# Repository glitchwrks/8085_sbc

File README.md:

# Glitch Works 8085 SBC

This repository contains the recovered EAGLE projects for the various PC boards designed as part of the Glitch Works 8085 SBC projects. These designs have been manufactured and tested and generally found to be functional; however, no warranty is made as to their fitness for any purpose. Please see the [LICENSE](https://github.com/glitchwrks/8085_sbc/blob/master/LICENSE) file for more information.

If you are interested in obtaining a bare circuit board, kit, or assembled board, please contact us through GitHub or [the Glitch Works contact form](https://services.theglitchworks.net/ng/messages/new). There's a chance we'll already have a bare board on hand, since later boards were ordered through [OSH Park](https://oshpark.com/) and resulted in three boards.

If you decide to produce any of these designs, or assemble a board from the provided schematics, please let us know through GitHub or [the Glitch Works contact form](https://services.theglitchworks.net/ng/messages/new).

### 8085 SBC rev 1

This is the original PC board produced from the "mess of wires" that started my exploration into the 8085 CPU! You can read more about the board's evolution and design [here](http://users.glitchwrks.com/~glitch/2010/09/02/8085-sbc). This board was meant to be the CPU board in a stack of boards, and contains 8K EPROM, 8K static RAM, an 8085, and associated clock generation and memory decode circuitry. You can flash a LED on the SOD pin with nothing more than this basic hardware.

### 8085 SBC rev 2

An extension of the rev 1 design, this board incorporates more RAM and ROM, mounting holes, and a few other features. Read about the board [here](http://users.glitchwrks.com/~glitch/2011/10/29/sbc-rev-2).

[AN0001 describes ROM jumpers](https://github.com/glitchwrks/8085_sbc/blob/master/8085_sbc_rev2/an0001_jumpers.txt) for socket IC3.

### I/O Board

This board contains a Zilog SCC (two channel USART) and Intel 8255 PPI to provide two serial ports and 24 bits of parallel I/O. It stacks on top of the 8085 SBC board, PC-104 style. Read about design and testing [here](http://users.glitchwrks.com/~glitch/2017/04/24/8085-io-board). I wrote a [ROM monitor](https://github.com/glitchwrks/gwmon-80) that works with this board. This was on display at [HOPE Number Nine](http://hope.net/) with the vintage computer guys.

There's an [ECO for old etches](https://github.com/glitchwrks/8085_sbc/blob/master/io_board/eco0007.txt) that is relevant if you got one of these boards from us before 2023. It corrects a routing error w.r.t. the 8255 PPI reset signal. See the linked writeup above for a picture documenting the fix.

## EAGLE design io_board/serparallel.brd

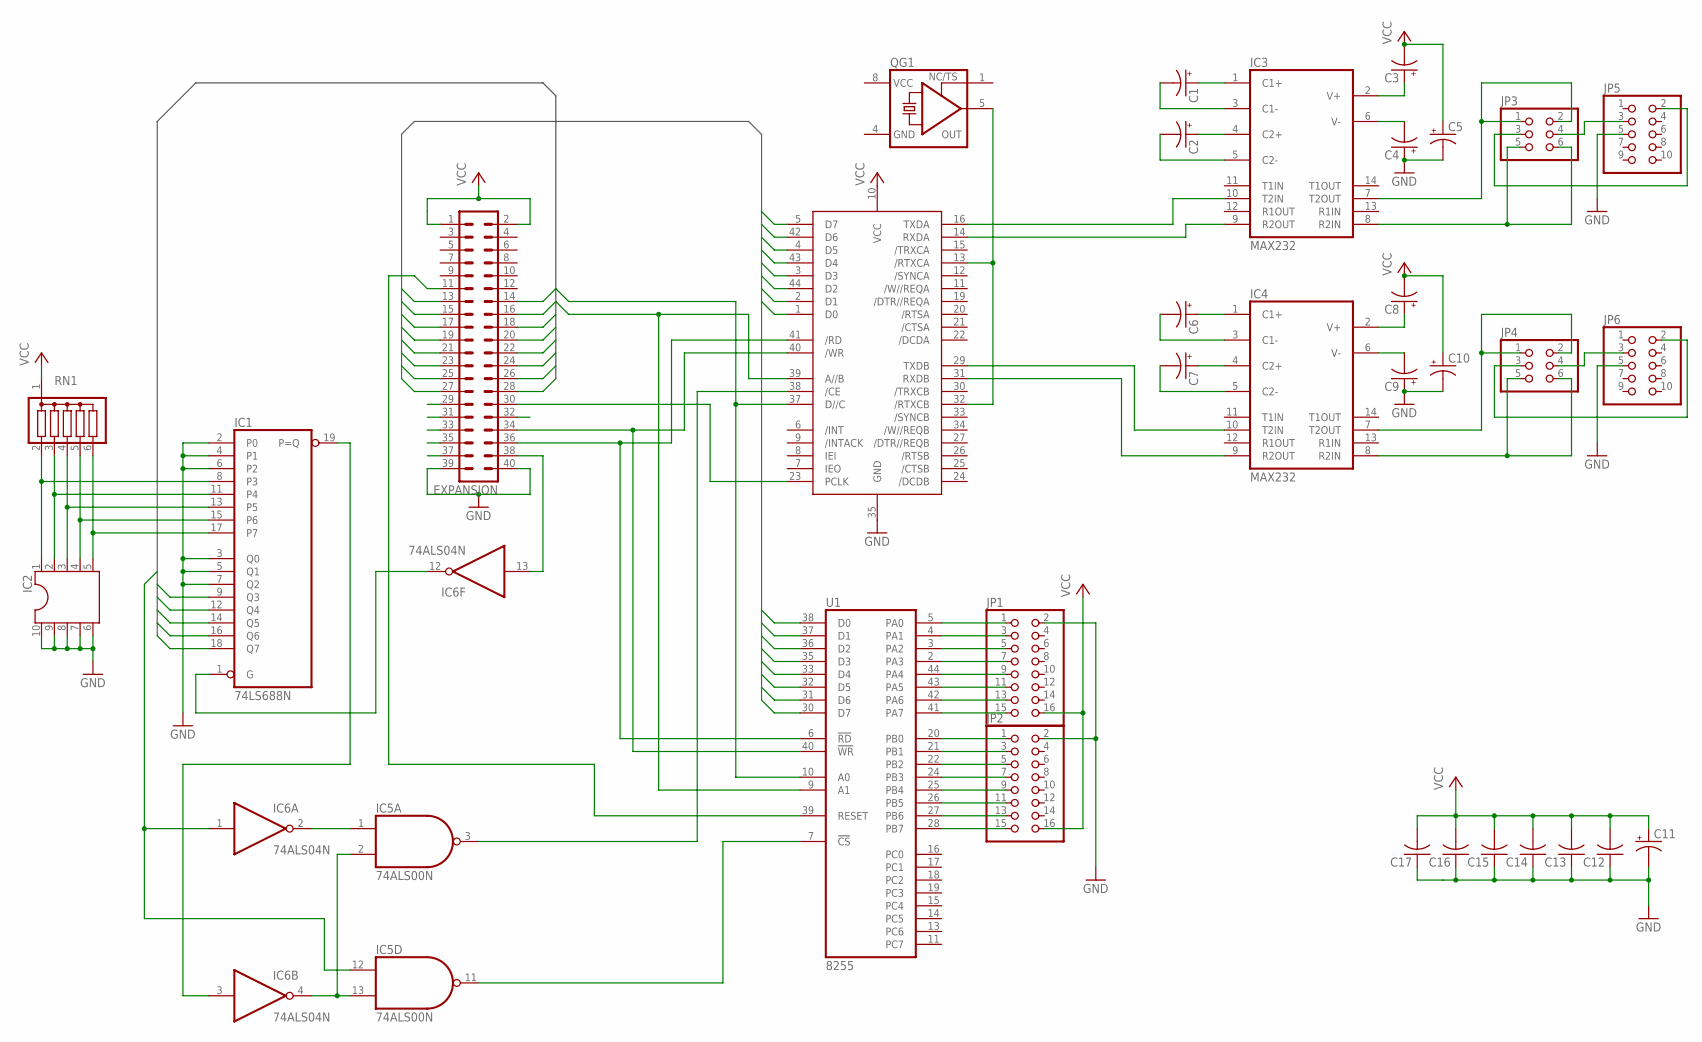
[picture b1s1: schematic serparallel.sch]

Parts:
C1, C2, C3, C4, C5, C6, C7, C8, C9, C10: CPOL-USE2,5-6E; E2,5-6E
C11: CPOL-USE15-6AXIAL; E15-6
C12, C13, C14, C15, C16, C17: C-US075-032X103; C075-032X103
EXPANSION: MA20-2W
IC1: 74LS688N; DIL20
IC2: DIL10
IC3, IC4: MAX232; DIL16
IC5: 74ALS00N; DIL14
IC6: 74ALS04N; DIL14
JP1, JP2: PINHD-2X8/90; 2X08/90
JP3, JP4: PINHD-2X3; 2X03
JP5, JP6: PINHD-2X5/90; 2X05/90
QG1: XO-8; DIL08S
RN1: G05R; SIL6
U1: 8255; S44
U2: Z8530; S44

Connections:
/RD: EXPANSION.36, U1.6 (!RD), U2.41 (/RD)
/WR: EXPANSION.34, U1.40 (!WR), U2.40 (/WR)
ADDRESS8: EXPANSION.14, U1.10 (A0), U2.37 (D//C)
ADDRESS9: EXPANSION.16, U1.9 (A1), U2.39 (A//B)
ADDRESS10: EXPANSION.18, IC5.12 (I0), IC6.1 (I)
ADDRESS11: EXPANSION.20, IC1.9 (Q3)
ADDRESS12: EXPANSION.22, IC1.12 (Q4)
ADDRESS13: EXPANSION.24, IC1.14 (Q5)
ADDRESS14: EXPANSION.26, IC1.16 (Q6)
ADDRESS15: EXPANSION.28, IC1.18 (Q7)
ALE: EXPANSION.32
CLKOUT: EXPANSION.30, U2.23 (PCLK)
DATA0: EXPANSION.27, U1.38 (D0), U2.1 (D0)
DATA1: EXPANSION.25, U1.37 (D1), U2.2 (D1)
DATA2: EXPANSION.23, U1.36 (D2), U2.44 (D2)
DATA3: EXPANSION.21, U1.35 (D3), U2.3 (D3)
DATA4: EXPANSION.19, U1.33 (D4), U2.43 (D4)
DATA5: EXPANSION.17, U1.32 (D5), U2.4 (D5)
DATA6: EXPANSION.15, U1.31 (D6), U2.42 (D6)
DATA7: EXPANSION.13, U1.30 (D7), U2.5 (D7)
GND: C4.+, C5.-, C9.+, C10.-, C11.-, C12.1, C13.1, C14.1, C15.1, C16.1, C17.1, EXPANSION.39, EXPANSION.40, IC1.2 (P0), IC1.3 (Q0), IC1.4 (P1), IC1.5 (Q1), IC1.6 (P2), IC1.7 (Q2), IC1.10 (GND), IC2.6, IC2.7, IC2.8, IC2.9, IC2.10, IC3.15 (GND), IC4.15 (GND), IC5.7 (GND), IC6.7 (GND), JP1.2, JP2.2, JP5.5, JP6.5, QG1.4 (GND), U1.8 (GND), U2.35 (GND)
INTBUS0: EXPANSION.37
INTBUS1: EXPANSION.35
INTBUS2: EXPANSION.33
INTBUS3: EXPANSION.31
INTBUS4: EXPANSION.29
IO/M: EXPANSION.38, IC6.13 (I)
unnamed: IC1.8 (P3), IC2.1, RN1.2
unnamed: IC1.11 (P4), IC2.2, RN1.3
unnamed: IC1.13 (P5), IC2.3, RN1.4
unnamed: IC1.15 (P6), IC2.4, RN1.5
unnamed: IC1.17 (P7), IC2.5, RN1.6
unnamed: IC5.1 (I0), IC6.2 (O)
unnamed: IC5.2 (I1), IC5.13 (I1), IC6.4 (O)
unnamed: C1.+, IC3.1 (C1+)
unnamed: C1.-, IC3.3 (C1-)
unnamed: C2.+, IC3.4 (C2+)
unnamed: C2.-, IC3.5 (C2-)
unnamed: C3.+, IC3.2 (V+)
unnamed: C4.-, IC3.6 (V-)
unnamed: C6.+, IC4.1 (C1+)
unnamed: IC5.3 (O), U2.38 (/CE)
unnamed: C6.-, IC4.3 (C1-)
unnamed: C7.+, IC4.4 (C2+)
unnamed: C7.-, IC4.5 (C2-)
unnamed: C8.+, IC4.2 (V+)
unnamed: C9.-, IC4.6 (V-)
unnamed: QG1.5 (OUT), U2.13 (/RTXCA), U2.32 (/RTXCB)
unnamed: IC3.10 (T2IN), U2.16 (TXDA)
unnamed: IC3.9 (R2OUT), U2.14 (RXDA)
unnamed: JP3.4, JP5.3
unnamed: JP3.3, JP5.2
unnamed: IC3.8 (R2IN), JP3.5, JP3.6
unnamed: JP1.1, U1.5 (PA0)
unnamed: IC3.7 (T2OUT), JP3.1, JP3.2
unnamed: JP1.3, U1.4 (PA1)
unnamed: JP1.5, U1.3 (PA2)
unnamed: JP1.7, U1.2 (PA3)
unnamed: JP1.9, U1.44 (PA4)
unnamed: JP1.11, U1.43 (PA5)
unnamed: JP1.13, U1.42 (PA6)
unnamed: JP1.15, U1.41 (PA7)
unnamed: JP2.1, U1.20 (PB0)
unnamed: JP2.3, U1.21 (PB1)
unnamed: JP2.5, U1.22 (PB2)
unnamed: JP2.7, U1.24 (PB3)
unnamed: JP2.9, U1.25 (PB4)
unnamed: JP2.11, U1.26 (PB5)
unnamed: JP2.13, U1.27 (PB6)
unnamed: JP2.15, U1.28 (PB7)
unnamed: IC5.11 (O), U1.7 (!CS)
unnamed: IC1.19 (P=Q), IC6.3 (I)
unnamed: IC1.1 (G), IC6.12 (O)
unnamed: JP4.4, JP6.3
unnamed: JP4.3, JP6.2
unnamed: IC4.7 (T2OUT), JP4.1, JP4.2
unnamed: IC4.8 (R2IN), JP4.5, JP4.6
unnamed: IC4.10 (T2IN), U2.29 (TXDB)
unnamed: IC4.9 (R2OUT), U2.31 (RXDB)
RESOUT: EXPANSION.11, U1.39 (RESET)
VCC: C3.-, C5.+, C8.-, C10.+, C11.+, C12.2, C13.2, C14.2, C15.2, C16.2, C17.2, EXPANSION.1, EXPANSION.2, IC1.20 (VCC), IC3.16 (VCC), IC4.16 (VCC), IC5.14 (VCC), IC6.14 (VCC), JP1.16, JP2.16, QG1.8 (VCC), RN1.1, U1.29 (VCC), U2.10 (VCC)

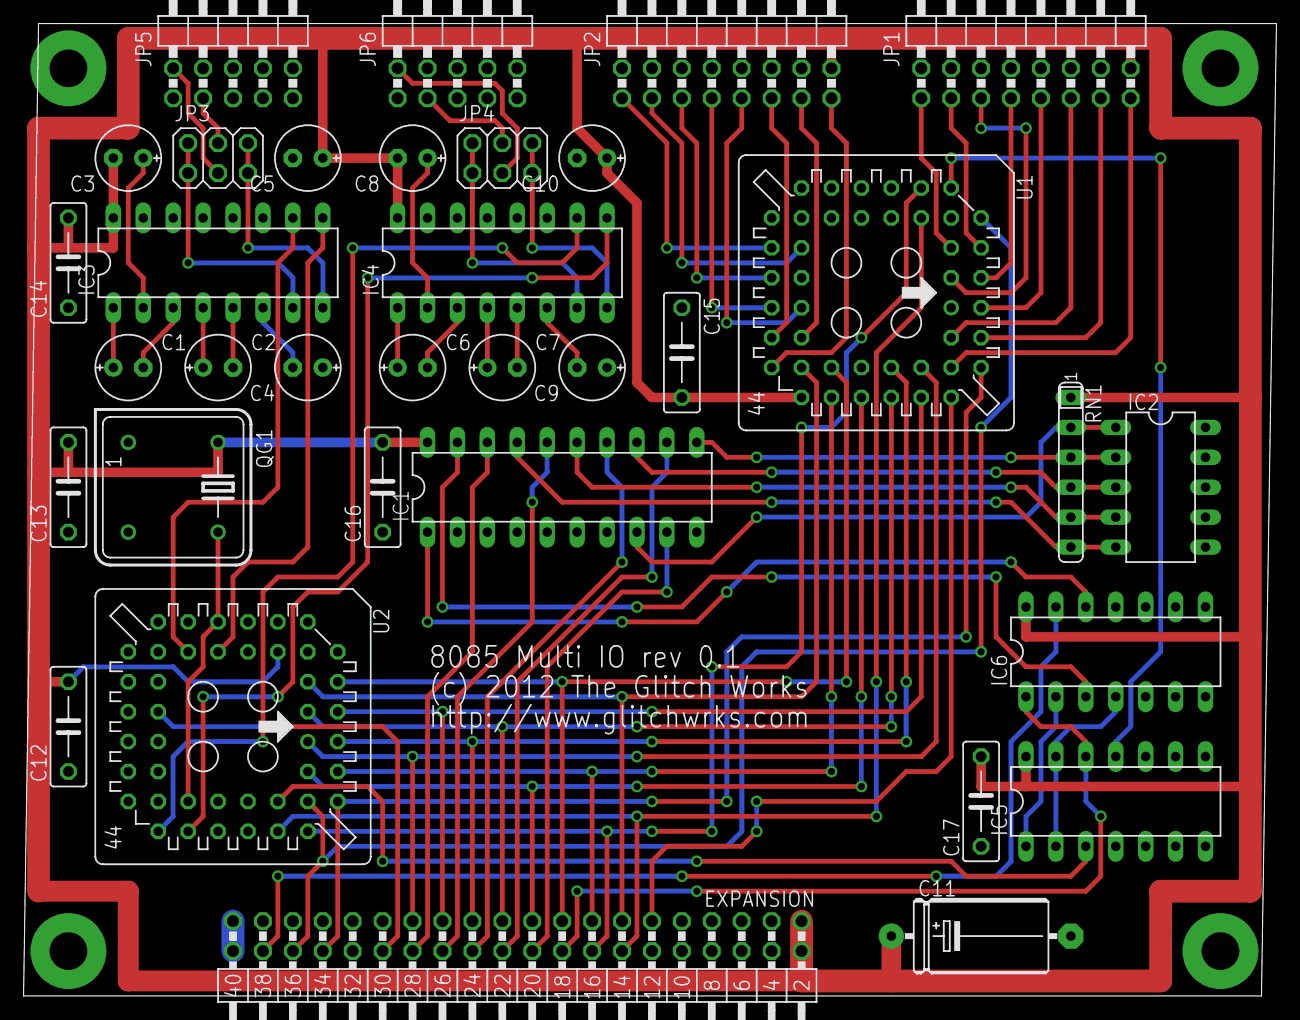
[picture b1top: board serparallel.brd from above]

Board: 2 copper layers, 106.3 x 82.5 mm, 34 parts (0 on the bottom side), 75 nets.

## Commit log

2017-02-07 Fixing contact form link
2017-05-16 Adding Multi-IO PNG schematic
2020-02-11 Adding PNG schematics for 8085 SBC rev 1,2
2023-03-26 Adding ECO0007 documenting PPI reset fix on Multi IO rev 0
2023-03-26 Adding Multi IO writeup link, updating links, linking to ECO0007
2023-03-27 Test commit
2023-03-27 Removing test file
2023-03-27 Adding appnote for 8085 SBC rev 2 ROM jumper options
2023-03-27 Adding AN0001 to README

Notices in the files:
io_board/serparallel.brd:
(c) 2012 The Glitch Works
